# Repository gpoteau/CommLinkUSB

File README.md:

CommLinkUSB
===========

CommLinkUSB is an open source USB adapter, it is effectively a replacement for the obsolete and hard to use ISA CommLink adapter.
It allows you to connect Action Replay, Game Hunter, or Clone card to a computer over USB.

License Information
-------------------

This project is derived from https://github.com/gpoteau/CommLinkUSB. However, the firmware and host software have been rewritten or replaced.

The hardware design is licensed under [![Creative Commons License] (https://i.creativecommons.org/l/by-sa/4.0/88x31.png) Creative Commons Attribution-ShareAlike 4.0 International License](http://creativecommons.org/licenses/by-sa/4.0/).  
The USB Stack used in the firmware is [LUFA](http://http://www.fourwalledcubicle.com/LUFA.php), created by Dean Camera.  
The CommLinkUSB firmware was created by Carsten Elton Sørensen.  
The CATFLAPU software is released under an unknown open source license. It is based on https://github.com/hkzlab/catflap4linux.

Repository Contents
-------------------
* **/Firmware**
    * CommLinkUSB.hex - Firmware for Atmega32u4 boards.
* **/Hardware** - Hardware design files for the CommLinkUSB. These files were designed in [Eagle](http://http://www.cadsoftusa.com/).
* **/Software** - Host software and Windows driver.

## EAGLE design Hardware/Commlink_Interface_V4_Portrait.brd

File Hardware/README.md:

CommLink Interface
=======

The main part of the hardware is a Atmega32u4. As it's only sale in smd package that not everyone can solder, I choose to use breakout board, the Atmega32u4 Breakout Board and the Teensy 2.0, that way we can use thru hole components.

Parts List
-------

| Part | Value |
| :-------------: | ----------- |
| C1 | 0.1uf |
| C2 | 0.1uf |
| C3 | 0.1uf |
| C4 | 180pf |
| IC1 | 74HC74N |
| IC2 | 74HC573N |
| IC3 | 74HC573N |
| JP1 | 2.54mm Pitch 2x13 Pin Dual Row Straight IDC Pin Headers |
| JP2 | **_(Optional)_** 2.54mm Pitch 1x14 Pin Single Row Straight IDC Pin Headers |
| LED | GREEN 3MM LED |
| R | 470 (220~470 lower value for brighter light) |
| Misc | Parallel LPT Printer Port Bracket to Motherboard 25 Pin Female Cable Adapter PC |
| MC | [Adafruit Atmega32u4 Breakout Board](http://www.adafruit.com/product/296) **_or_** [PJRC Teensy 2.0 USB Development Board](https://www.pjrc.com/store/teensy.html) |

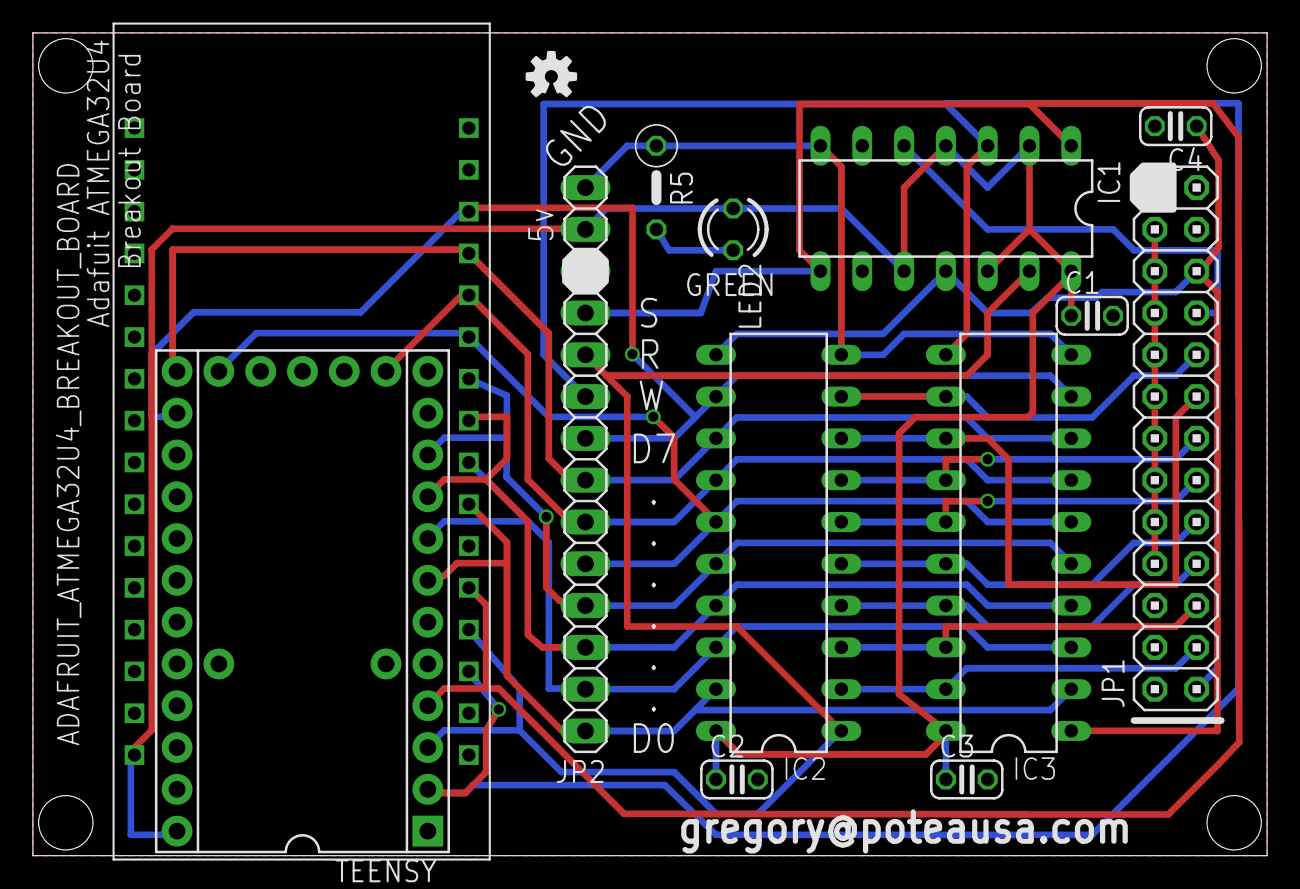
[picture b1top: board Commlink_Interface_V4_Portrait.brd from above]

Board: 4 copper layers, 75.0 x 50.0 mm, 18 parts (0 on the bottom side), 24 nets.

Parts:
ADAFRUIT_ATMEGA32U4_BREAKOUT_BOARD: Adafruit ATMEGA32U4; ATMEGA32U4BREAKOUT
C1, C2, C3: 0.1uf; C025-024X044
C4: 180pf; C025-024X044
H1, H2, H3, H4: STAND-OFF
IC1: 74LS74N; DIL14
IC2, IC3: 74AS573N; DIL20
JP1: PAR's DB25; 2X13
JP2: PC; 1X14
LED2: GREEN; LED3MM
LOGO_OPEN_HARDWARE: OSHW-LOGO-S
R5: 470; 0207/5V
TEENSY: TEENSY 2.0; TEENSY

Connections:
GND: ADAFRUIT_ATMEGA32U4_BREAKOUT_BOARD.GND, ADAFRUIT_ATMEGA32U4_BREAKOUT_BOARD.GND2, C1.2, C2.2, C3.2, C4.2, IC1.7, IC2.10, IC3.10, JP1.8, JP1.10, JP1.12, JP1.14, JP1.16, JP1.18, JP1.20, JP1.22, JP1.24, JP2.14, R5.1, TEENSY.GND, TEENSY.GRND1
unnamed: LED2.K, R5.2
unnamed: IC2.3, IC3.18, JP1.5
unnamed: IC2.4, IC3.17, JP1.7
unnamed: IC2.5, IC3.16, JP1.9
unnamed: IC2.6, IC3.15, JP1.11
unnamed: IC2.7, IC3.14, JP1.13
unnamed: IC2.8, IC3.13, JP1.15
unnamed: IC2.2, IC3.19, JP1.3
unnamed: IC2.9, IC3.12, JP1.17
PAR_ACK: C4.1, IC1.11, IC2.11, IC3.1, JP1.21
PAR_STB: IC1.5, JP1.1, JP1.19
PCRD#: ADAFRUIT_ATMEGA32U4_BREAKOUT_BOARD.B1, IC1.13, IC2.1, JP2.10, TEENSY.B1
PCWR: ADAFRUIT_ATMEGA32U4_BREAKOUT_BOARD.B0, IC1.3, IC3.11, JP2.9, TEENSY.B0
PC_D0: ADAFRUIT_ATMEGA32U4_BREAKOUT_BOARD.D0, IC2.19, IC3.2, JP2.1, TEENSY.D0
PC_D1: ADAFRUIT_ATMEGA32U4_BREAKOUT_BOARD.D1, IC2.18, IC3.3, JP2.2, TEENSY.D1
PC_D2: ADAFRUIT_ATMEGA32U4_BREAKOUT_BOARD.D2, IC2.17, IC3.4, JP2.3, TEENSY.D2
PC_D3: ADAFRUIT_ATMEGA32U4_BREAKOUT_BOARD.D3, IC2.16, IC3.5, JP2.4, TEENSY.D3
PC_D4: ADAFRUIT_ATMEGA32U4_BREAKOUT_BOARD.D4, IC2.15, IC3.6, JP2.5, TEENSY.D4
PC_D5: ADAFRUIT_ATMEGA32U4_BREAKOUT_BOARD.D5, IC2.14, IC3.7, JP2.6, TEENSY.D5
PC_D6: ADAFRUIT_ATMEGA32U4_BREAKOUT_BOARD.D6, IC2.13, IC3.8, JP2.7, TEENSY.D6
PC_D7: ADAFRUIT_ATMEGA32U4_BREAKOUT_BOARD.D7, IC2.12, IC3.9, JP2.8, TEENSY.D7
STATUS: ADAFRUIT_ATMEGA32U4_BREAKOUT_BOARD.B2, IC1.1, IC1.8, JP2.11, TEENSY.B2
VCC: ADAFRUIT_ATMEGA32U4_BREAKOUT_BOARD.5V, C1.1, C2.1, C3.1, IC1.2, IC1.4, IC1.10, IC1.12, IC1.14, IC2.20, IC3.20, JP2.13, LED2.A, TEENSY.+5V

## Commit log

2015-07-03 update, end user software's name change
2015-07-03 name change, first release.
2015-07-03 Hardware pics, initial commit
2015-07-03 update, add pics.
2015-07-21 Faulty
2015-07-28 PCB pic,initial commit.
2015-08-25 Fix Led issue
2016-02-14 Ver 0.18 added - usage message. - N Switch Execute without hooks. - K Switch Pause before execute. - T<num(hex)> Switch Tasks vault (def=4) - E<num(hex)> Switch Event value (default=10) - S<num(hex)>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
    Check EXE file header
    changed
    - D<adr(hex)> Switch Upload to address.
2018-07-01 Self signing driver script
2018-07-18 Added BulkVendor sample
2018-07-18 Implemented basic PAR support
2018-07-19 Working firmware and tiny test program. Device ID is now BAD2, it's incompatible with the original project
2018-07-19 Added catflap4linux source
2018-07-19 Switch to CMake
2018-07-19 Fixed compiler warnings
2018-07-20 Removed a bunch of unnecessary XPlorer code and low level comms
2018-07-20 Compiles and links
2018-07-20 catflapu reset tested and working

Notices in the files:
README.md:
License Information:
The hardware design is licensed under [ (https://i.creativecommons.org/l/by-sa/4.0/88x31.png) Creative Commons Attribution-ShareAlike 4.0 International License](http://creativecommons.org/licenses/by-sa/4.0/).
parts and their libraries:
SparkFun-Aesthetics: Licensing: Creative Commons ShareAlike 4.0 International - https://creativecommons.org/licenses/by-sa/4.0
SparkFun: Licensing: CC v3.0 Share-Alike You are welcome to use this library for commercial purposes.
